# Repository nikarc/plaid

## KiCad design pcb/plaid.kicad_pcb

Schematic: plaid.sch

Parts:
C1, C2: 20p; C_Disc_D3.0mm_W1.6mm_P2.50mm
C3: 4.7u; CP_Radial_D4.0mm_P1.50mm
C4, C5, C6: 100n; C_Disc_D4.3mm_W1.9mm_P5.00mm
D1, D2, D3, D4, D5, D6, D7, D8, D9, D10, D11, D12, D13, D14, D15, D16, D17, D18, D19, D20, D21, D22, D23, D24, D25, D26, D27, D28, D29, D30, D31, D32, D33, D34, D35, D36, D37, D38, D39, D40, D41, D42, D43, D44, D45, D46: 1N4148; D_DO-35_SOD27_P5.08mm_Horizontal
D49: SK6812; LED_SK6812_PLCC4_5.0x5.0mm_P3.2mm
D51, D52: 3.6V; D_DO-35_SOD27_P5.08mm_Horizontal
F2: 500mA; polyfuse_5.1mm
H1, H2, H3, H4, H5, H6, H7, H8, H9, H10: M2; MountingHole_2.2mm_M2_Pad
J2: AVR_ISP_6; Pin_Header_Straight_2x03_Pitch2.54mm
R4: 10k; R_Axial_DIN0204_L3.6mm_D1.6mm_P5.08mm_Horizontal
R9: 1.5k; R_Axial_DIN0204_L3.6mm_D1.6mm_P5.08mm_Horizontal
R10, R11: 5.1k; R_Axial_DIN0204_L3.6mm_D1.6mm_P5.08mm_Horizontal
R12, R13: 75R; R_Axial_DIN0204_L3.6mm_D1.6mm_P5.08mm_Horizontal
SW1, SW2, SW3, SW4, SW5, SW6, SW7, SW8, SW9, SW10, SW11, SW12, SW13, SW14, SW15, SW16, SW17, SW18, SW19, SW20, SW21, SW22, SW23, SW24, SW25, SW26, SW27, SW28, SW29, SW30, SW31, SW32, SW33, SW34, SW35, SW36, SW37, SW38, SW39, SW40, SW43, SW44, SW45, SW46: SW_Push; SW_Cherry_MX1A_1.00u_PCB
SW41, SW42: SW_Push; SW_Cherry_MX1A_2.00u_PCBNOSCREEN
SW50: RESET; SW_PUSH_6mm
SW51: BOOT; SW_PUSH_6mm
U1: ATMEGA328-PU; DIP-28_W7.62mm
USB1: Type-C_USB_C_GCT_USB4085; USB_C_GCT_USB4085
Y1: 16MHz; Crystal_HC49-4H_Vertical

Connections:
+5V: C3.1, C4.1, C5.1, C6.2, D49.3, F2.1, J2.2, R4.1, R9.1, U1.7, U1.20
/COL0: SW1.2, SW13.2, SW25.2, SW37.2, U1.14
/COL1: SW2.2, SW14.2, SW26.2, SW38.2, U1.13
/COL2: SW3.2, SW15.2, SW27.2, SW39.2, U1.12
/COL3: SW4.2, SW16.2, SW28.2, SW40.2, SW51.1, U1.11
/COL4: SW5.2, SW17.2, SW29.2, SW41.2, U1.16
/COL5: SW6.2, SW18.2, SW30.2, SW42.2, U1.15
/COL6: SW7.2, SW19.2, SW31.2, SW43.1, U1.23
/COL7: SW8.2, SW20.2, SW32.2, SW44.2, U1.24
/COL8: SW9.2, SW21.2, SW33.2, SW45.2, U1.25
/COL9: SW10.2, SW22.2, SW34.2, SW46.2, U1.26
/COL10: SW11.2, SW23.2, SW35.2, U1.3
/COL11: SW12.2, SW24.2, SW36.2, U1.2
/RESET: J2.5, R4.2, SW50.1, U1.1
/RGB_LED: D49.2, U1.27
/ROW0: D1.1, D2.1, D3.1, D4.1, D5.1, D6.1, D7.1, D8.1, D9.1, D10.1, D11.1, D12.1, J2.1, U1.18
/ROW1: D13.1, D14.1, D15.1, D16.1, D17.1, D18.1, D19.1, D20.1, D21.1, D22.1, D23.1, D24.1, J2.3, U1.19
/ROW2: D25.1, D26.1, D27.1, D28.1, D29.1, D30.1, D31.1, D32.1, D33.1, D34.1, D35.1, D36.1, J2.4, U1.17
/ROW3: D37.1, D38.1, D39.1, D40.1, D41.1, D42.1, D43.1, D44.1, D45.1, D46.1, U1.6
/USB_D+: R13.1, U1.4
/USB_D-: R12.1, U1.5
GND: C1.2, C2.2, C3.2, C4.2, C5.2, C6.1, D49.1, D51.2 (A), D52.2 (A), J2.6, R10.1, R11.2, SW50.2, SW51.2, U1.8, U1.22, USB1.A1 (GND), USB1.A12 (GND), USB1.B1 (GND), USB1.B12 (GND), USB1.S1 (SHIELD)
unnamed: C1.1, U1.10, Y1.2
unnamed: C2.1, U1.9, Y1.1
unnamed: D1.2, SW1.1
unnamed: D2.2, SW2.1
unnamed: D3.2, SW3.1
unnamed: D4.2, SW4.1
unnamed: D5.2, SW5.1
unnamed: D6.2, SW6.1
unnamed: D7.2, SW7.1
unnamed: D8.2, SW8.1
unnamed: D9.2, SW9.1
unnamed: D10.2, SW10.1
unnamed: D11.2, SW11.1
unnamed: D12.2, SW12.1
unnamed: D13.2, SW13.1
unnamed: D14.2, SW14.1
unnamed: D15.2, SW15.1
unnamed: D16.2, SW16.1
unnamed: D17.2, SW17.1
unnamed: D18.2, SW18.1
unnamed: D19.2, SW19.1
unnamed: D20.2, SW20.1
unnamed: D21.2, SW21.1
unnamed: D22.2, SW22.1
unnamed: D23.2, SW23.1
unnamed: D24.2, SW24.1
unnamed: D25.2, SW25.1
unnamed: D26.2, SW26.1
unnamed: D27.2, SW27.1
unnamed: D28.2, SW28.1
unnamed: D29.2, SW29.1
unnamed: D30.2, SW30.1
unnamed: D31.2, SW31.1
unnamed: D32.2, SW32.1
unnamed: D33.2, SW33.1
unnamed: D34.2, SW34.1
unnamed: D35.2, SW35.1
unnamed: D36.2, SW36.1
unnamed: D37.2, SW37.1
unnamed: D38.2, SW38.1
unnamed: D39.2, SW39.1
unnamed: D40.2, SW40.1
unnamed: D41.2, SW41.1
unnamed: D42.2, SW42.1
unnamed: D43.2, SW43.2
unnamed: D44.2, SW44.1
unnamed: D45.2, SW45.1
unnamed: D46.2, SW46.1
unnamed: D51.1 (K), R9.2, R12.2, USB1.A7 (DN1), USB1.B7 (DN2)
unnamed: D52.1 (K), R13.2, USB1.A6 (DP1), USB1.B6 (DP2)
unnamed: R10.2, USB1.A5 (CC1)
unnamed: R11.1, USB1.B5 (CC2)
VCC: F2.2, USB1.A4 (VBUS), USB1.A9 (VBUS), USB1.B4 (VBUS), USB1.B9 (VBUS)

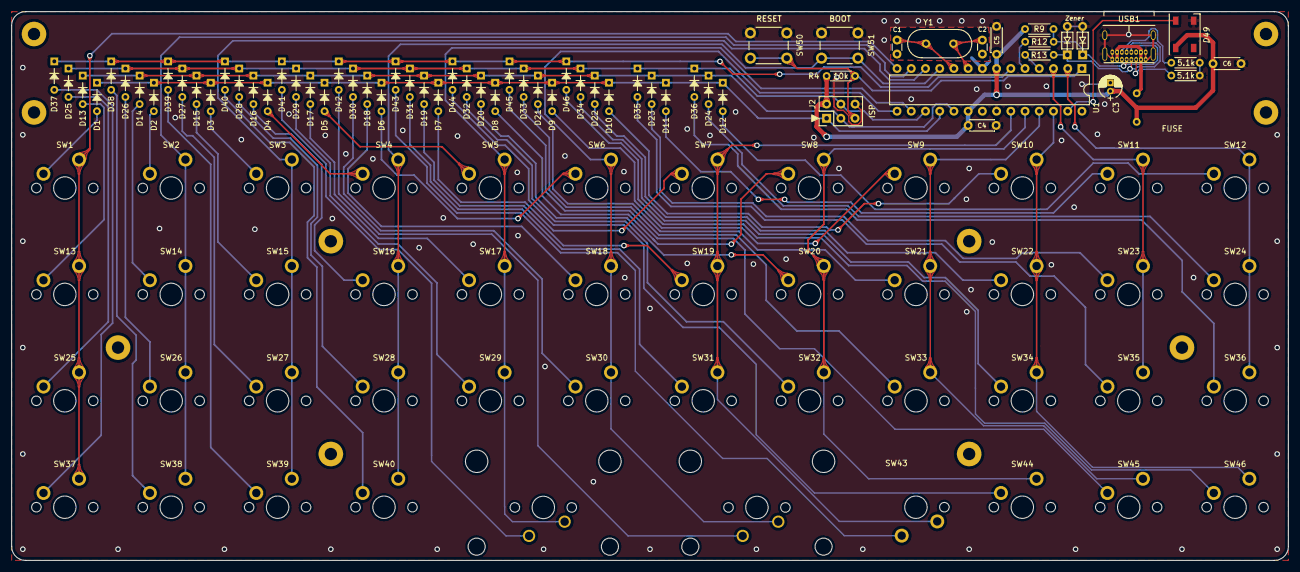
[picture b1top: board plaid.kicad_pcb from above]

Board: 2 copper layers, 228.0 x 98.0 mm, 124 parts (0 on the bottom side), 75 nets.

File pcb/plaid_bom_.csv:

Component,Description,Part,References,Value,Footprint,Quantity Per PCB,Datasheet
1,"Unpolarized capacitor, small symbol",C_Small,C4 C5,100n,C_Disc_D4.3mm_W1.9mm_P5.00mm,2,~
2,"Unpolarized capacitor, small symbol",C_Small,C6,100n,C_Disc_D4.3mm_W1.9mm_P5.00mm,1,~
3,"Unpolarized capacitor, small symbol",C_Small,C1 C2,20p,C_Disc_D3.0mm_W1.6mm_P2.50mm,2,~
4,"Polarized capacitor, small US symbol",CP1_Small,C3,4.7u,CP_Radial_D4.0mm_P1.50mm,1,~
5,"Diode, small symbol, filled shape",D_Small_ALT,D1 D2 D3 D4 D5 D6 D7 D8 D9 D10 D11 D12 D13 D14 D15 D16 D17 D18 D19 D20 D21 D22 D23 D24 D25 D26 D27 D28 D29 D30 D31 D32 D33 D34 D35 D36 D37 D38 D39 D40 D41 D42 D43 D44 D45 D46,1N4148,D_DO-35_SOD27_P5.08mm_Horizontal,46,~
6,"Zener diode, small symbol",D_Zener_Small,D51 D52,3.6V,D_DO-35_SOD27_P5.08mm_Horizontal,2,~
7,RGB LED with integrated controller,SK6812,D49,SK6812,LED_SK6812_PLCC4_5.0x5.0mm_P3.2mm,1,https://cdn-shop.adafruit.com/product-files/1138/SK6812+LED+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
8,"Resettable fuse, polymeric positive temperature coefficient, small symbol",Polyfuse_Small,F2,500mA,polyfuse_5.1mm,1,~
9,"Generic connector, double row, 02x03, odd/even pin numbering scheme (row 1 odd numbers, row 2 even numbers), script generated (kicad-library-utils/schlib/autogen/connector/)",Conn_02x03_Odd_Even,J2,AVR_ISP_6,Pin_Header_Straight_2x03_Pitch2.54mm,1,~
10,"Resistor, small symbol",R_Small,R9,1.5k,R_Axial_DIN0204_L3.6mm_D1.6mm_P5.08mm_Horizontal,1,~
11,"Resistor, small symbol",R_Small,R4,10k,R_Axial_DIN0204_L3.6mm_D1.6mm_P5.08mm_Horizontal,1,~
12,"Resistor, small symbol",R_Small,R10 R11,5.1k,R_Axial_DIN0204_L3.6mm_D1.6mm_P5.08mm_Horizontal,2,~
13,"Resistor, small symbol",R_Small,R12 R13,75R,R_Axial_DIN0204_L3.6mm_D1.6mm_P5.08mm_Horizontal,2,~
14,"Push button switch, generic, two pins",SW_Push,SW51,BOOT,SW_PUSH_6mm,1,
15,"Push button switch, generic, two pins",SW_Push,SW50,RESET,SW_PUSH_6mm,1,
16,"Push button switch, generic, two pins",SW_Push,SW1 SW2 SW3 SW4 SW5 SW6 SW7 SW8 SW9 SW10 SW11 SW12 SW13 SW14 SW15 SW16 SW17 SW18 SW19 SW20 SW21 SW22 SW23 SW24 SW25 SW26 SW27 SW28 SW29 SW30 SW31 SW32 SW33 SW34 SW35 SW36 SW37 SW38 SW39 SW40 SW43 SW44 SW45 SW46,SW_Push,SW_Cherry_MX1A_1.00u_PCB,44,
17,"Push button switch, generic, two pins",SW_Push,SW41 SW42,SW_Push,SW_Cherry_MX1A_2.00u_PCBNOSCREEN,2,
18,"20MHz, 32kB Flash, 2kB SRAM, 1kB EEPROM, DIP-28",ATmega328P-PU,U1,ATMEGA328-PU,DIP-28_W7.62mm,1,http://www.atmel.com/images/atmel-8271-8-bit-avr-microcontro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
19,,Type-C_USB_C_GCT_USB4085,USB1,Type-C_USB_C_GCT_USB4085,USB_C_GCT_USB4085,1,
20,"Two pin crystal, small symbol",Crystal_Small,Y1,16MHz,Crystal_HC49-4H_Vertical,1,~





Component Groups:,20
Component Count:,114
Fitted Components:,114
Number of PCBs:,1
Total components:,114
Schematic Version:,
Schematic Date:,
PCB Variant:,default
BoM Date:,"Wednesday, December 25, 2019 at 11:41:12 AM"
Schematic Source:,/Users/nicholasarcuri/Documents/kicad/plaid/pcb/plaid.sch
KiCad Version:,Eeschema (5.1.4-0-10_14)

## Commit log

2019-12-24 Switch to USB-C
2019-12-24 RGB LED setup
2020-01-07 Add usb-c, rgb led

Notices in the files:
pcb/plaid.kicad_pcb:
(c)2019 Takuya Urakawa, Dm9Records.com
